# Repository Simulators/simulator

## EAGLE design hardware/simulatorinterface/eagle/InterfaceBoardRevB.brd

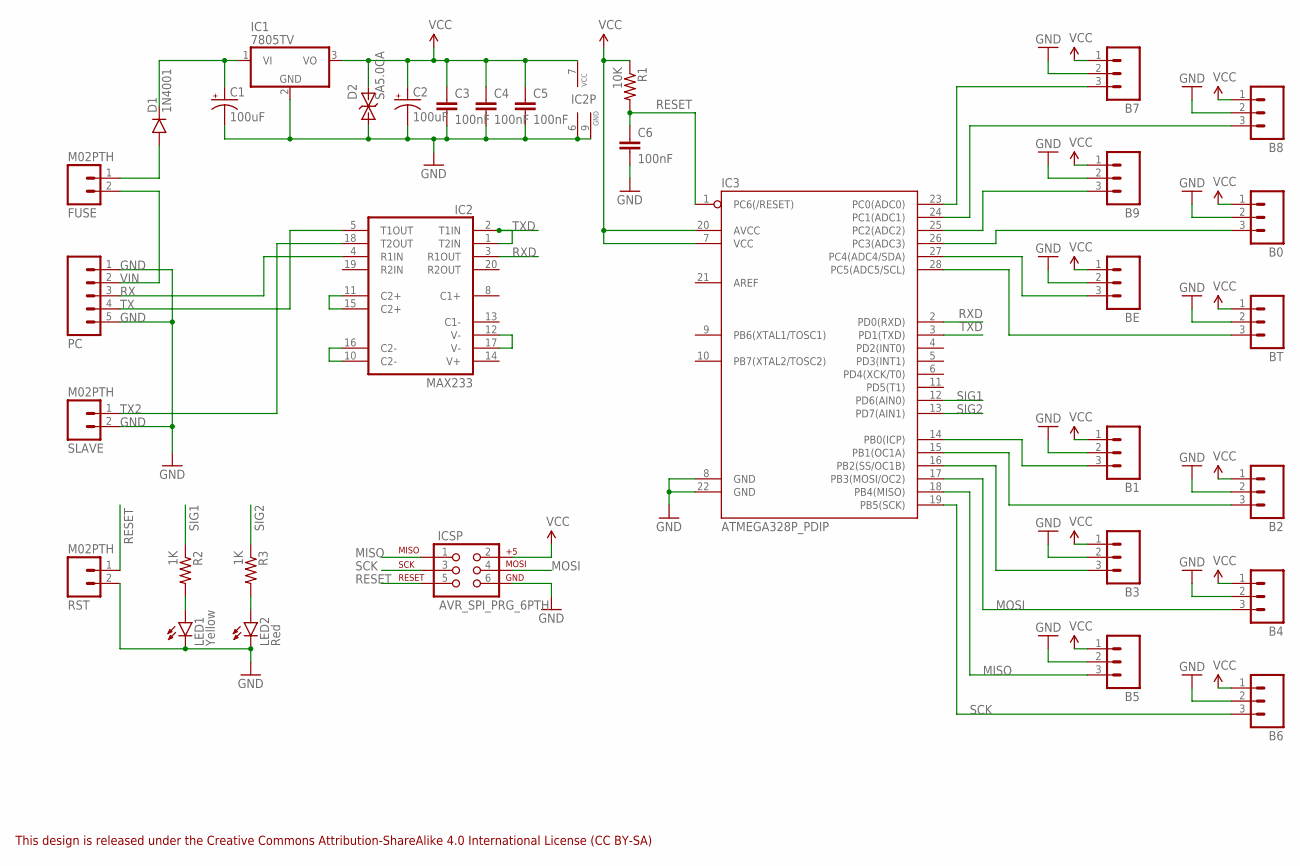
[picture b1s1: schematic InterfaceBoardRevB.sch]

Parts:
B0, B1, B2, B3, B4, B5, B6, B7, B8, B9: M03PTH; 1X03
BE: M03PTH; 1X03
BT: M03PTH; 1X03
C1, C2: 100uF; CPOL-RADIAL-100UF-25V
C3, C4, C5, C6: 100nF; CAP-PTH-SMALL
D1: 1N4001; DO41_DIODE
D2: SA5.0CA; DO41_TVS
FUSE: M02PTH; 1X02
IC1: 7805TV; TO220V
IC2: MAX233; DIL20
IC3: ATMEGA328P_PDIP; DIL28-3
ICSP: AVR_SPI_PRG_6PTH; 2X3
LED1: Yellow; LED3MM_LARGEHOLES
LED2: Red; LED3MM_LARGEHOLES
PC: M05PTH; 1X05
R1: 10K; AXIAL-0.4
R2, R3: 1K; AXIAL-0.4
RST: M02PTH; 1X02
SLAVE: M02PTH; 1X02

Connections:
GND: B0.2, B1.2, B2.2, B3.2, B4.2, B5.2, B6.2, B7.2, B8.2, B9.2, BE.2, BT.2, C1.2 (-), C2.2 (-), C3.2, C4.2, C5.2, C6.2, D2.A, IC1.2 (GND), IC2.6 (GND), IC2.9 (GND), IC3.8 (GND), IC3.22 (GND), ICSP.6, LED1.K (C), LED2.K (C), PC.1, PC.5, RST.2, SLAVE.2
MISO: B5.3, IC3.18 (PB4(MISO)), ICSP.1
MOSI: B4.3, IC3.17 (PB3(MOSI/OC2)), ICSP.4
unnamed: B7.3, IC3.23 (PC0(ADC0))
unnamed: B8.3, IC3.24 (PC1(ADC1))
unnamed: B9.3, IC3.25 (PC2(ADC2))
unnamed: B0.3, IC3.26 (PC3(ADC3))
unnamed: BT.3, IC3.28 (PC5(ADC5/SCL))
unnamed: BE.3, IC3.27 (PC4(ADC4/SDA))
unnamed: LED1.A, R2.P$2 (2)
unnamed: IC2.10 (C2-), IC2.16 (C2-)
unnamed: B3.3, IC3.16 (PB2(SS/OC1B))
unnamed: B2.3, IC3.15 (PB1(OC1A))
unnamed: B1.3, IC3.14 (PB0(ICP))
unnamed: IC2.11 (C2+), IC2.15 (C2+)
unnamed: IC2.12 (V-), IC2.17 (V-)
unnamed: D1.A, FUSE.1
unnamed: LED2.A, R3.P$2 (2)
unnamed: C1.1 (+), D1.C, IC1.1 (VI)
RESET: C6.1, IC3.1 (PC6(/RESET)), ICSP.5, R1.P$2 (2), RST.1
RX: IC2.4 (R1IN), PC.3
RXD: IC2.3 (R1OUT), IC3.2 (PD0(RXD))
SCK: B6.3, IC3.19 (PB5(SCK)), ICSP.3
SIG1: IC3.12 (PD6(AIN0)), R2.P$1 (1)
SIG2: IC3.13 (PD7(AIN1)), R3.P$1 (1)
TX: IC2.5 (T1OUT), PC.4
TX2: IC2.18 (T2OUT), SLAVE.1
TXD: IC2.1 (T2IN), IC2.2 (T1IN), IC3.3 (PD1(TXD))
VCC: B0.1, B1.1, B2.1, B3.1, B4.1, B5.1, B6.1, B7.1, B8.1, B9.1, BE.1, BT.1, C2.1 (+), C3.1, C4.1, C5.1, D2.C, IC1.3 (VO), IC2.7 (VCC), IC3.7 (VCC), IC3.20 (AVCC), ICSP.2, R1.P$1 (1)
VIN: FUSE.2, PC.2

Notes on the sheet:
This design is released under the Creative Commons Attribution-ShareAlike 4.0 International License (CC BY-SA)

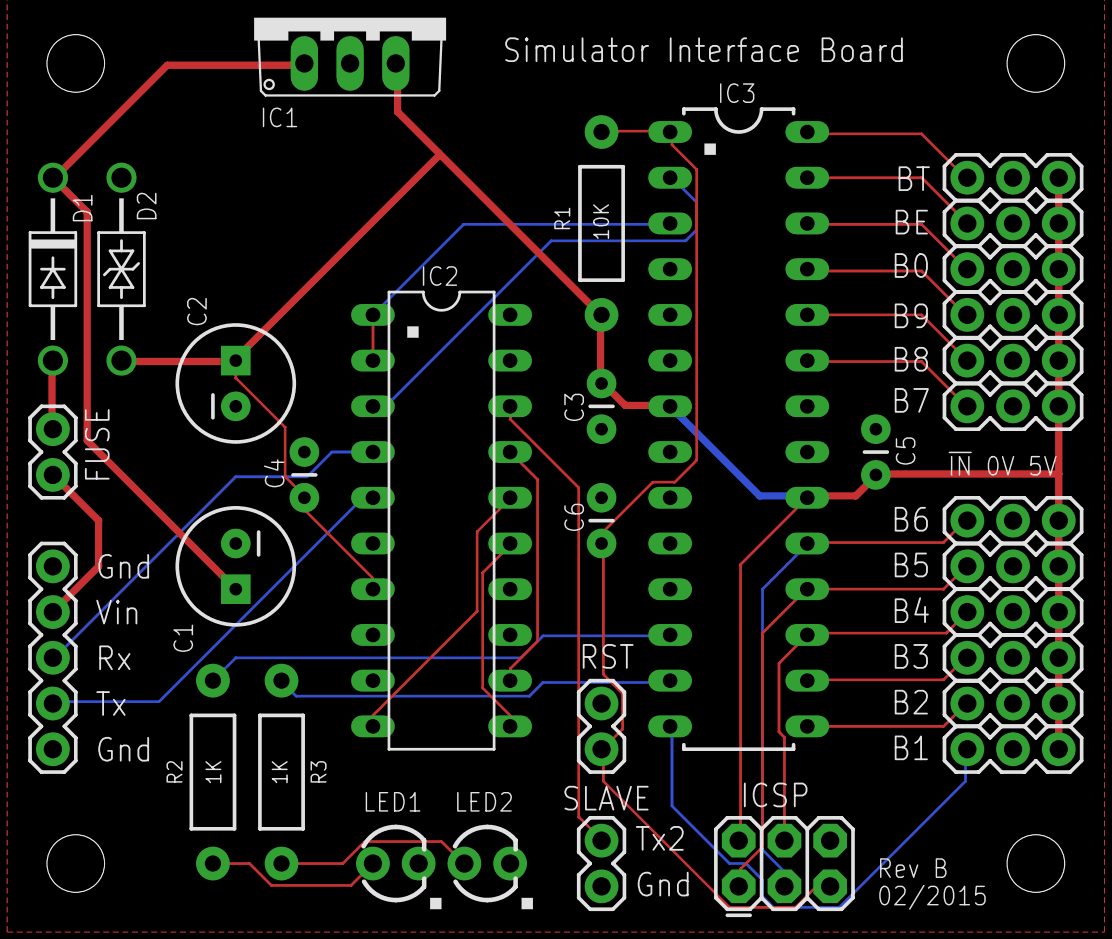
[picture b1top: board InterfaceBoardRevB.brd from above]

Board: 2 copper layers, 33 parts (0 on the bottom side), 30 nets.

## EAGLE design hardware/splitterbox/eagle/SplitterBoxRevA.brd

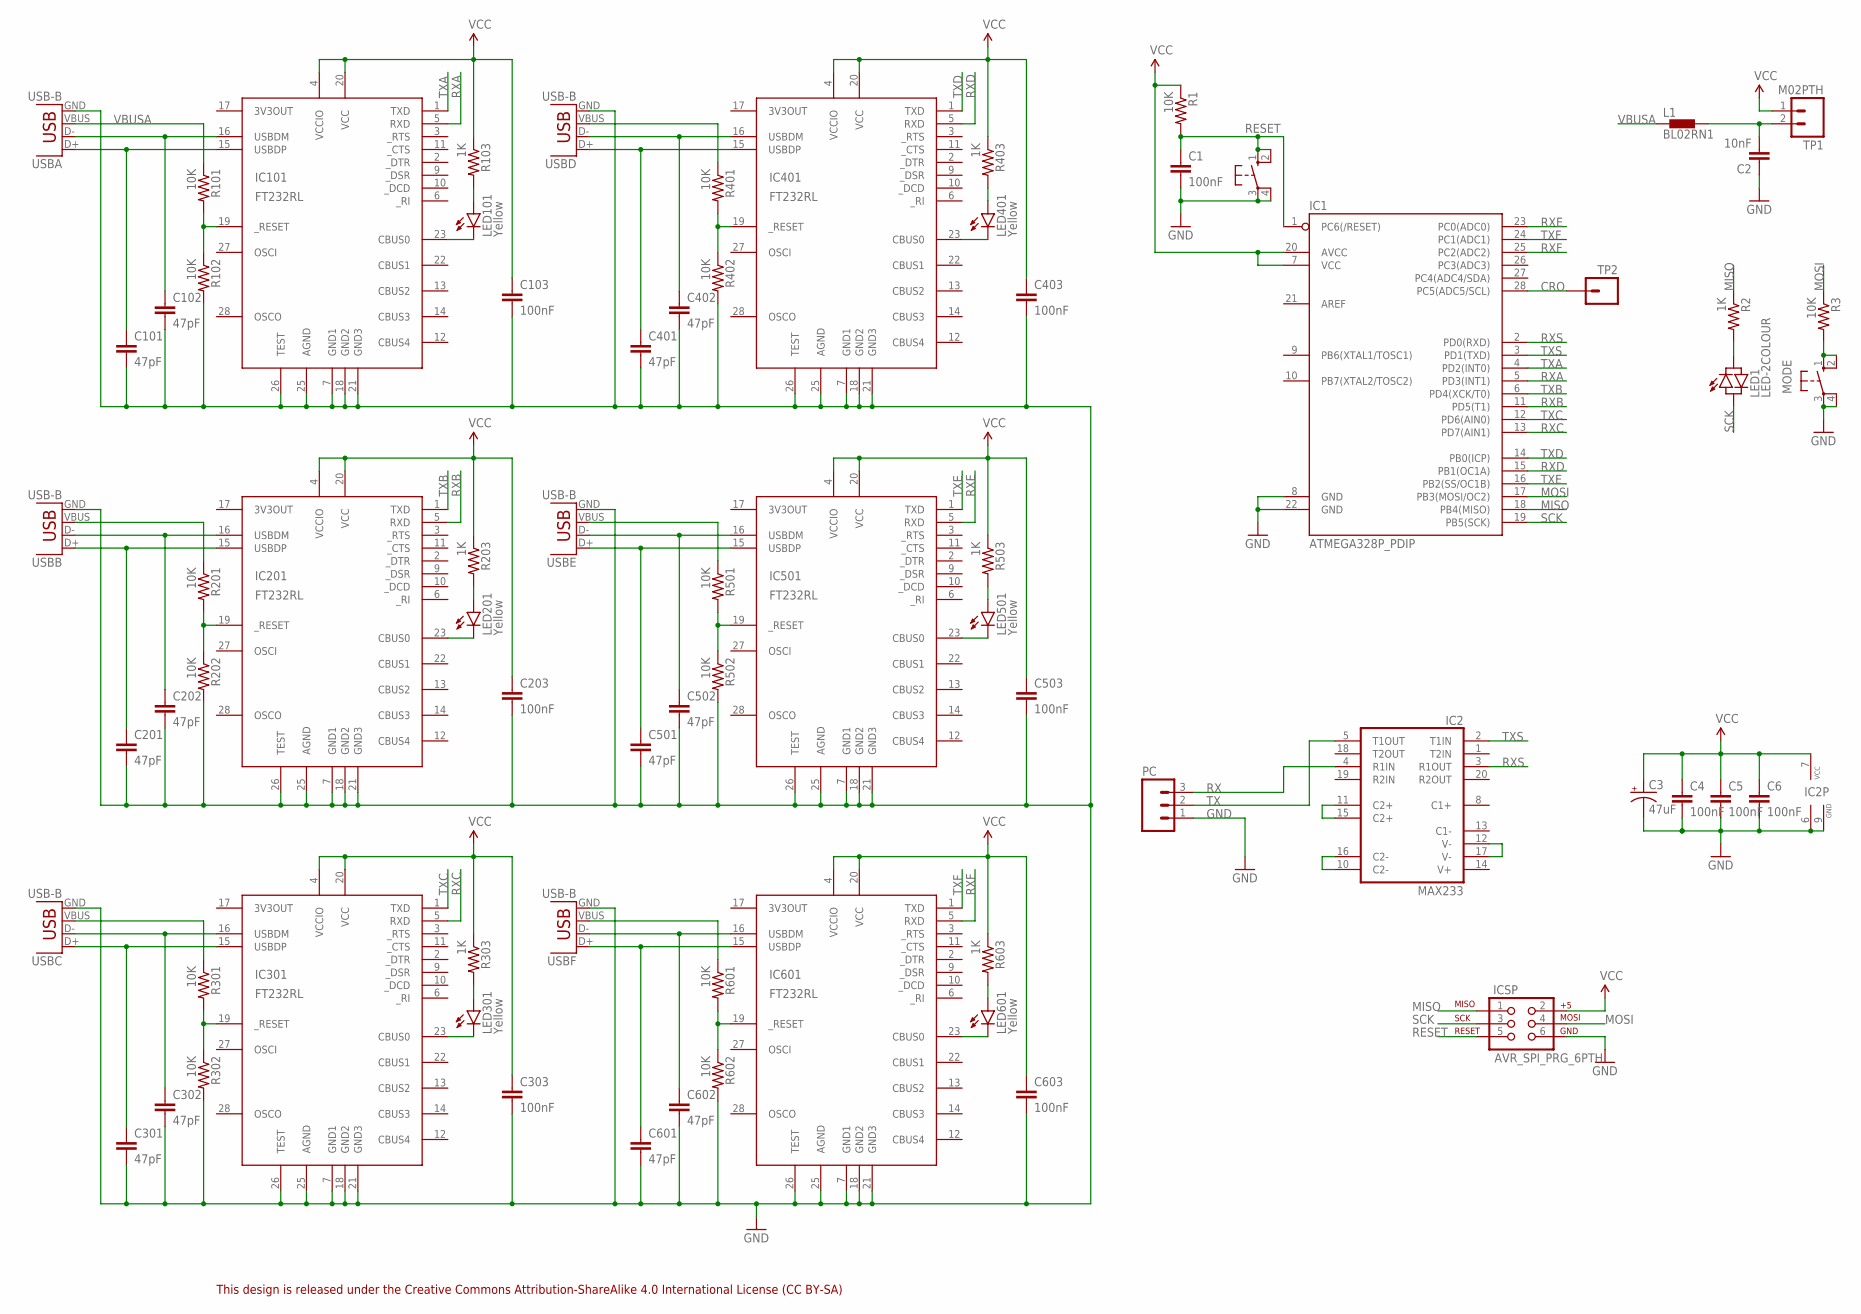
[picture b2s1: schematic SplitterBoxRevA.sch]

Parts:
C1, C4, C5, C6, C103, C203, C303, C403, C503, C603: 100nF; CAP-PTH-SMALL
C2: 10nF; CAP-PTH-SMALL
C3: 47uF; CPOL-RADIAL-100UF-25V
C101, C102, C201, C202, C301, C302, C401, C402, C501, C502, C601, C602: 47pF; CAP-PTH-SMALL
IC1: ATMEGA328P_PDIP; DIL28-3
IC2: MAX233; DIL20
IC101, IC201, IC301, IC401, IC501, IC601: FT232RL; SSOP28DB
ICSP: AVR_SPI_PRG_6PTH; 2X3
L1: BL02RN1
LED1: LED-2COLOUR; LED3MM
LED101, LED201, LED301, LED401, LED501, LED601: Yellow; LED3MM_LARGEHOLES
MODE: 10-XX; B3F-10XX
PC: M03PTH; 1X03
R1, R3, R101, R102, R201, R202, R301, R302, R401, R402, R501, R502, R601, R602: 10K; AXIAL-0.4
R2, R103, R203, R303, R403, R503, R603: 1K; AXIAL-0.4
RST: 10-XX; B3F-10XX
TP1: M02PTH; 1X02
TP2: M01PTH; 1X01
USBA: USB-B; USB-B-PTH
USBB: USB-B; USB-B-PTH
USBC: USB-B; USB-B-PTH
USBD: USB-B; USB-B-PTH
USBE: USB-B; USB-B-PTH
USBF: USB-B; USB-B-PTH

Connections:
CRO: IC1.28 (PC5(ADC5/SCL)), TP2.1
GND: C1.2, C2.1, C3.2 (-), C4.2, C5.2, C6.2, C101.2, C102.2, C103.2, C201.2, C202.2, C203.2, C301.2, C302.2, C303.2, C401.2, C402.2, C403.2, C501.2, C502.2, C503.2, C601.2, C602.2, C603.2, IC1.8 (GND), IC1.22 (GND), IC2.6 (GND), IC2.9 (GND), IC101.7 (GND1), IC101.18 (GND2), IC101.21 (GND3), IC101.25 (AGND), IC101.26 (TEST), IC201.7 (GND1), IC201.18 (GND2), IC201.21 (GND3), IC201.25 (AGND), IC201.26 (TEST), IC301.7 (GND1), IC301.18 (GND2), IC301.21 (GND3), IC301.25 (AGND), IC301.26 (TEST), IC401.7 (GND1), IC401.18 (GND2), IC401.21 (GND3), IC401.25 (AGND), IC401.26 (TEST), IC501.7 (GND1), IC501.18 (GND2), IC501.21 (GND3), IC501.25 (AGND), IC501.26 (TEST), IC601.7 (GND1), IC601.18 (GND2), IC601.21 (GND3), IC601.25 (AGND), IC601.26 (TEST), ICSP.6, MODE.3, MODE.4 (P1), PC.1, R102.P$2 (2), R202.P$2 (2), R302.P$2 (2), R402.P$2 (2), R502.P$2 (2), R602.P$2 (2), RST.3, RST.4 (P1), USBA.GND, USBB.GND, USBC.GND, USBD.GND, USBE.GND, USBF.GND
MISO: IC1.18 (PB4(MISO)), ICSP.1, R2.P$1 (1)
MOSI: IC1.17 (PB3(MOSI/OC2)), ICSP.4, R3.P$1 (1)
unnamed: C201.1, IC201.15 (USBDP), USBB.D+
unnamed: C202.1, IC201.16 (USBDM), USBB.D-
unnamed: IC201.19 (_RESET), R201.P$2 (2), R202.P$1 (1)
unnamed: LED201.A, R203.P$2 (2)
unnamed: IC201.23 (CBUS0), LED201.K (C)
unnamed: C401.1, IC401.15 (USBDP), USBD.D+
unnamed: C402.1, IC401.16 (USBDM), USBD.D-
unnamed: MODE.1 (S), MODE.2 (S1), R3.P$2 (2)
unnamed: IC2.10 (C2-), IC2.16 (C2-)
unnamed: C2.2, L1.2, TP1.2
unnamed: IC2.11 (C2+), IC2.15 (C2+)
unnamed: IC2.12 (V-), IC2.17 (V-)
unnamed: IC401.19 (_RESET), R401.P$2 (2), R402.P$1 (1)
unnamed: LED401.A, R403.P$2 (2)
unnamed: IC401.23 (CBUS0), LED401.K (C)
unnamed: C301.1, IC301.15 (USBDP), USBC.D+
unnamed: C302.1, IC301.16 (USBDM), USBC.D-
unnamed: R201.P$1 (1), USBB.VBUS
unnamed: IC301.19 (_RESET), R301.P$2 (2), R302.P$1 (1)
unnamed: LED301.A, R303.P$2 (2)
unnamed: IC301.23 (CBUS0), LED301.K (C)
unnamed: R301.P$1 (1), USBC.VBUS
unnamed: C101.1, IC101.15 (USBDP), USBA.D+
unnamed: C102.1, IC101.16 (USBDM), USBA.D-
unnamed: IC101.19 (_RESET), R101.P$2 (2), R102.P$1 (1)
unnamed: LED101.A, R103.P$2 (2)
unnamed: IC101.23 (CBUS0), LED101.K (C)
unnamed: R401.P$1 (1), USBD.VBUS
unnamed: C501.1, IC501.15 (USBDP), USBE.D+
unnamed: C502.1, IC501.16 (USBDM), USBE.D-
unnamed: IC501.19 (_RESET), R501.P$2 (2), R502.P$1 (1)
unnamed: LED501.A, R503.P$2 (2)
unnamed: IC501.23 (CBUS0), LED501.K (C)
unnamed: R501.P$1 (1), USBE.VBUS
unnamed: C601.1, IC601.15 (USBDP), USBF.D+
unnamed: C602.1, IC601.16 (USBDM), USBF.D-
unnamed: IC601.19 (_RESET), R601.P$2 (2), R602.P$1 (1)
unnamed: LED601.A, R603.P$2 (2)
unnamed: IC601.23 (CBUS0), LED601.K (C)
unnamed: R601.P$1 (1), USBF.VBUS
unnamed: LED1.A, R2.P$2 (2)
RESET: C1.1, IC1.1 (PC6(/RESET)), ICSP.5, R1.P$2 (2), RST.1 (S), RST.2 (S1)
RX: IC2.4 (R1IN), PC.3
RXA: IC1.5 (PD3(INT1)), IC101.5 (RXD)
RXB: IC1.11 (PD5(T1)), IC201.5 (RXD)
RXC: IC1.13 (PD7(AIN1)), IC301.5 (RXD)
RXD: IC1.15 (PB1(OC1A)), IC401.5 (RXD)
RXE: IC1.23 (PC0(ADC0)), IC501.5 (RXD)
RXF: IC1.25 (PC2(ADC2)), IC601.5 (RXD)
RXS: IC1.2 (PD0(RXD)), IC2.3 (R1OUT)
SCK: IC1.19 (PB5(SCK)), ICSP.3, LED1.K (C)
TX: IC2.5 (T1OUT), PC.2
TXA: IC1.4 (PD2(INT0)), IC101.1 (TXD)
TXB: IC1.6 (PD4(XCK/T0)), IC201.1 (TXD)
TXC: IC1.12 (PD6(AIN0)), IC301.1 (TXD)
TXD: IC1.14 (PB0(ICP)), IC401.1 (TXD)
TXE: IC1.16 (PB2(SS/OC1B)), IC501.1 (TXD)
TXF: IC1.24 (PC1(ADC1)), IC601.1 (TXD)
TXS: IC1.3 (PD1(TXD)), IC2.2 (T1IN)
VBUSA: L1.1, R101.P$1 (1), USBA.VBUS
VCC: C3.1 (+), C4.1, C5.1, C6.1, C103.1, C203.1, C303.1, C403.1, C503.1, C603.1, IC1.7 (VCC), IC1.20 (AVCC), IC2.7 (VCC), IC101.4 (VCCIO), IC101.20 (VCC), IC201.4 (VCCIO), IC201.20 (VCC), IC301.4 (VCCIO), IC301.20 (VCC), IC401.4 (VCCIO), IC401.20 (VCC), IC501.4 (VCCIO), IC501.20 (VCC), IC601.4 (VCCIO), IC601.20 (VCC), ICSP.2, R1.P$1 (1), R103.P$1 (1), R203.P$1 (1), R303.P$1 (1), R403.P$1 (1), R503.P$1 (1), R603.P$1 (1), TP1.1

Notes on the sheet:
This design is released under the Creative Commons Attribution-ShareAlike 4.0 International License (CC BY-SA)

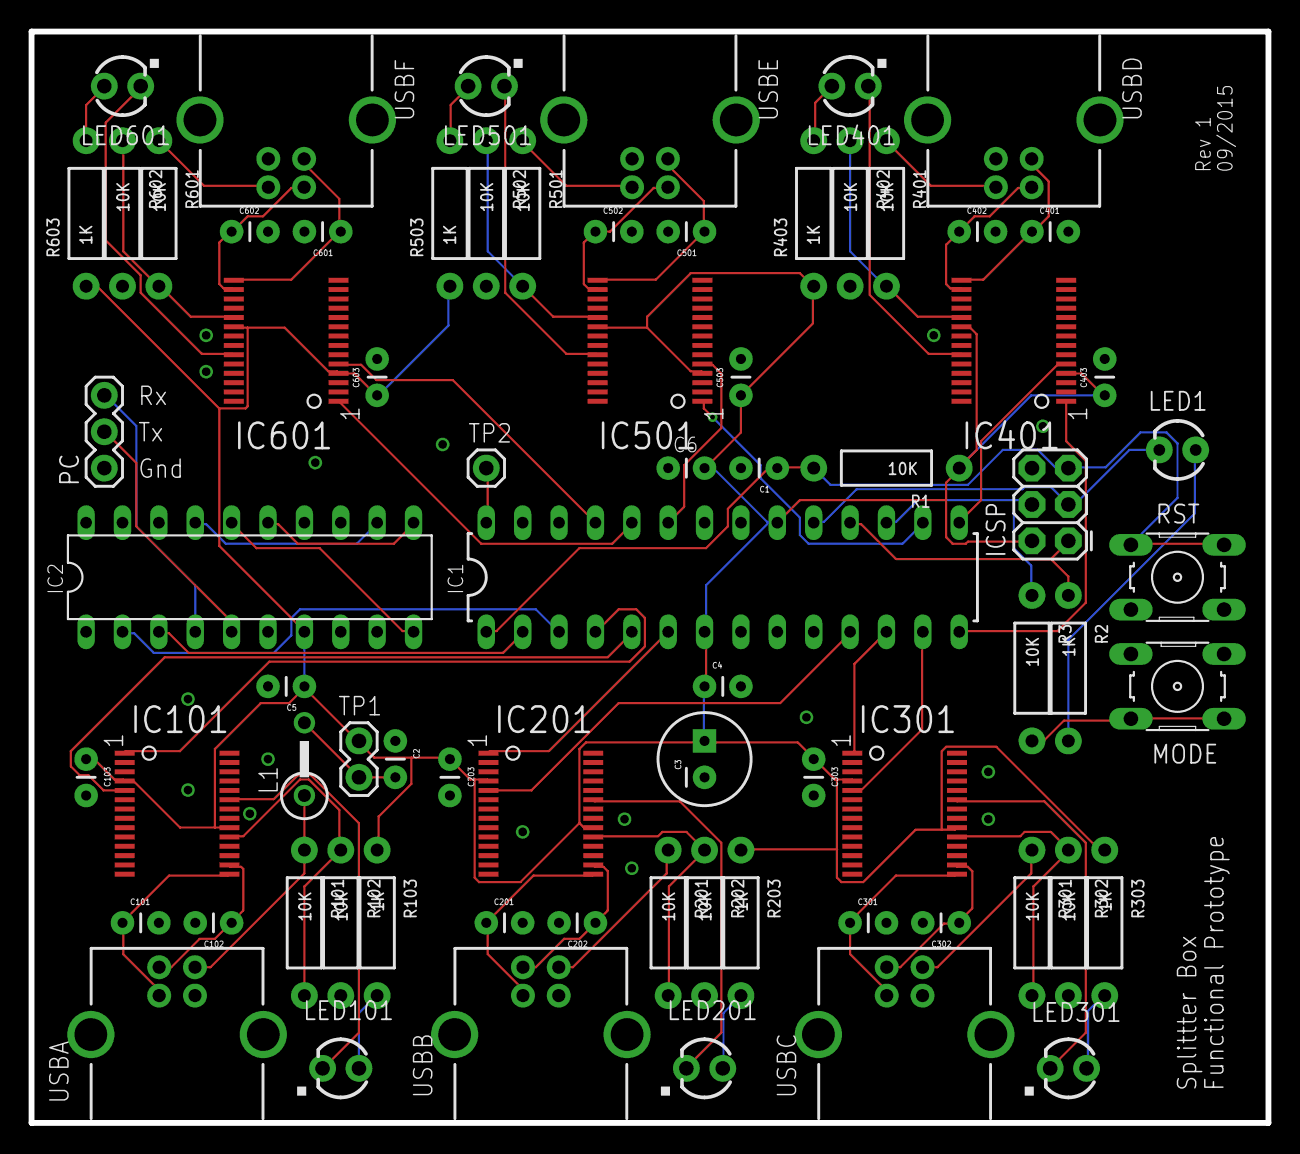
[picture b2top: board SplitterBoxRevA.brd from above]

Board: 2 copper layers, 86.4 x 76.2 mm, 73 parts (0 on the bottom side), 65 nets.

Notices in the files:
parts and their libraries:
SparkFun-DigitalIC: Licensing: Creative Commons ShareAlike 4.0 International - https://creativecommons.org/licenses/by-sa/4.0
